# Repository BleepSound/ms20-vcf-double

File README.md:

[![CC BY-SA 4.0][cc-by-sa-shield]][cc-by-sa]

# Double MS20-VCF

Latest documentation available at https://bleepsound.github.io/modules/

This work is licensed under a
[Creative Commons Attribution-ShareAlike 4.0 International License][cc-by-sa].

[![CC BY-SA 4.0][cc-by-sa-image]][cc-by-sa]

[cc-by-sa]: http://creativecommons.org/licenses/by-sa/4.0/
[cc-by-sa-image]: https://licensebuttons.net/l/by-sa/4.0/88x31.png
[cc-by-sa-shield]: https://img.shields.io/badge/License-CC%20BY--SA%204.0-lightgrey.svg

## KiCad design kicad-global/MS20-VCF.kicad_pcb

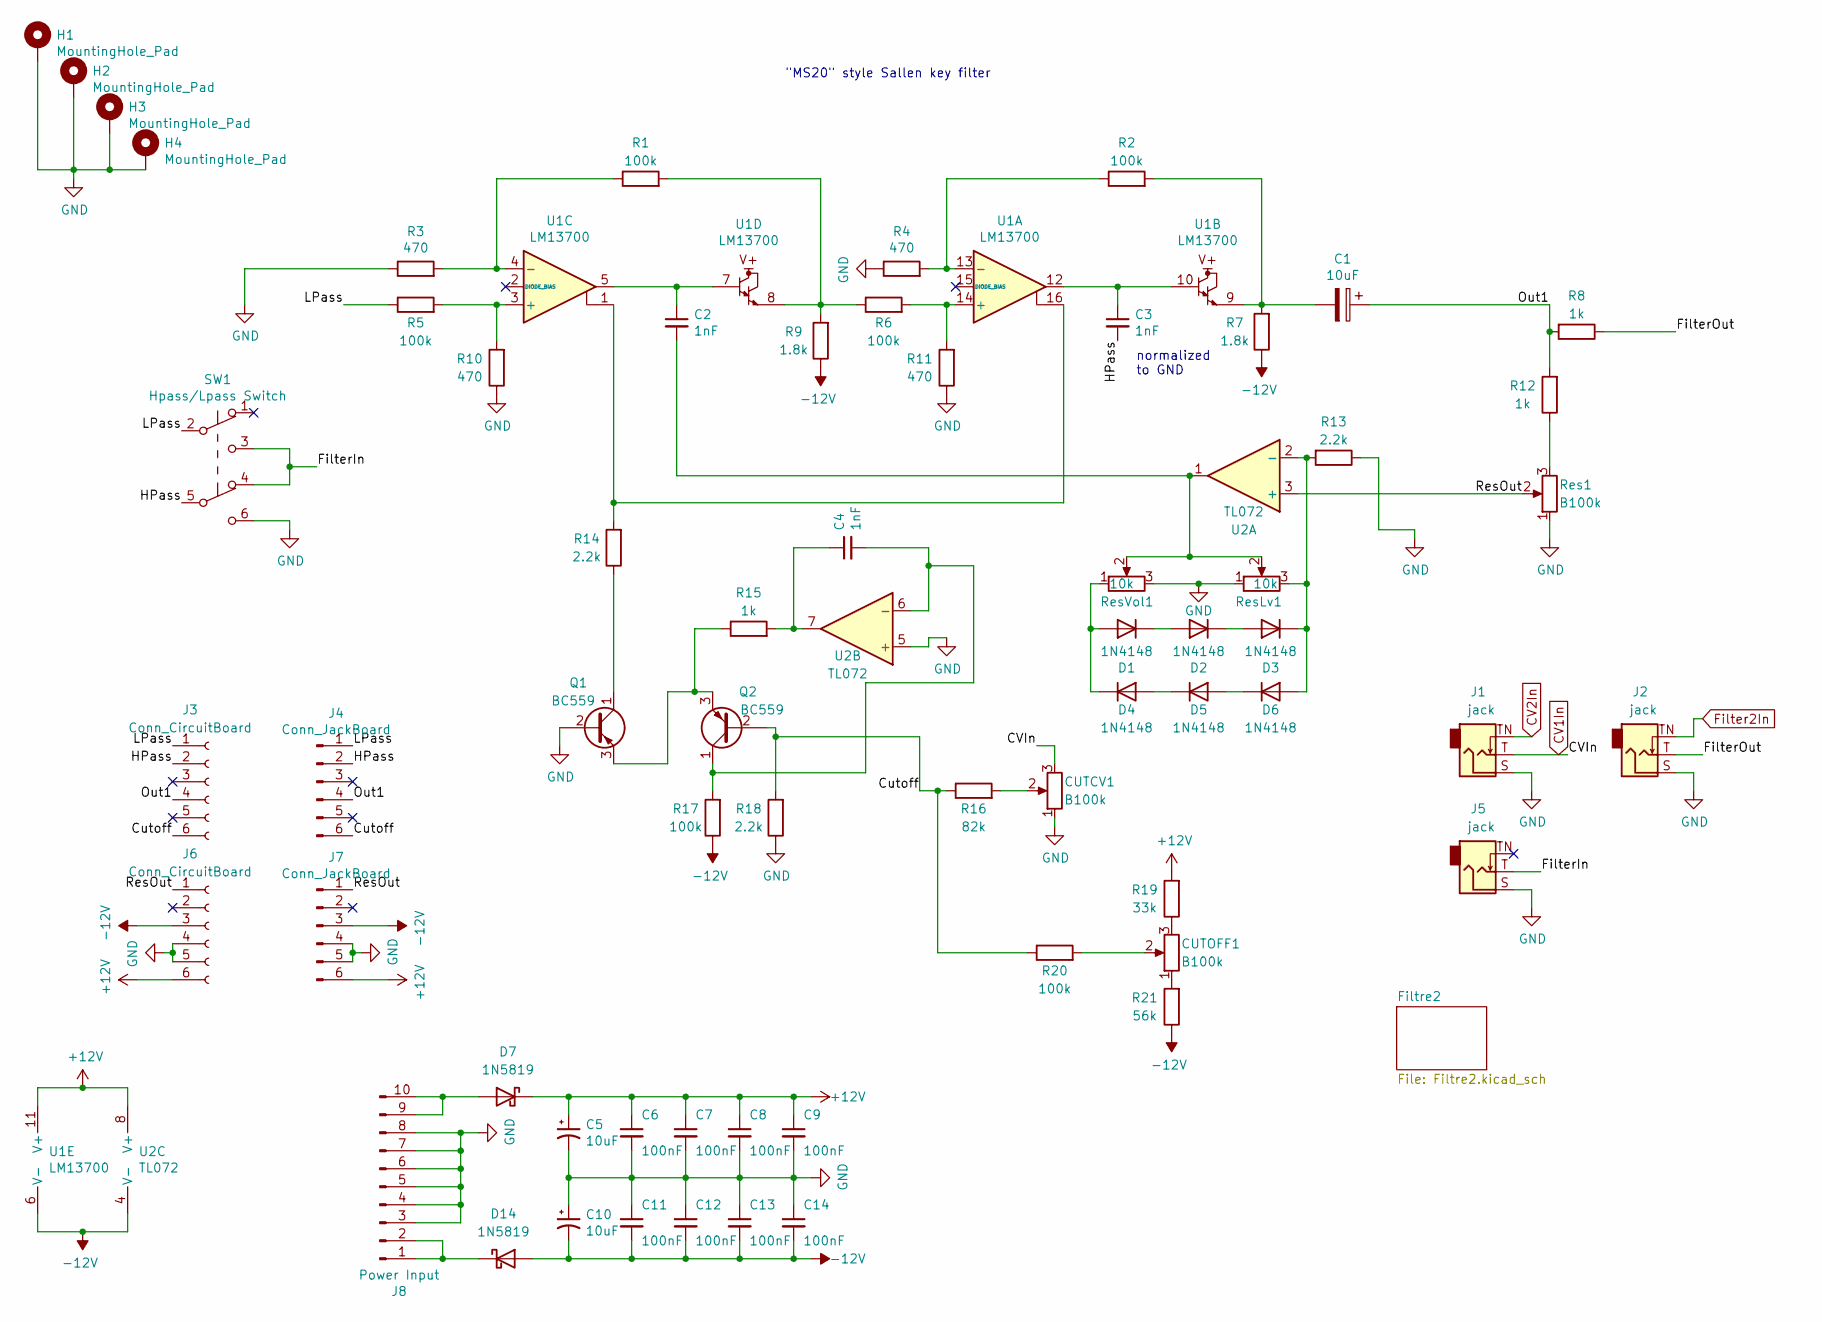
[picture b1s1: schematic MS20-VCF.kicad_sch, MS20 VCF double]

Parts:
C1, C5, C10: 10uF; CP_Radial_D5.0mm_P2.00mm
C2, C3, C4: 1nF; C_Disc_D7.0mm_W2.5mm_P5.00mm
C6, C7, C8, C9, C11, C12, C13, C14: 100nF; C_Disc_D7.0mm_W2.5mm_P5.00mm
CUTCV1: B100k; Pot-bourns-alpha
CUTOFF1: B100k; Pot-bourns-alpha
D1, D2, D3, D4, D5, D6: 1N4148; D_DO-35_SOD27_P7.62mm_Horizontal
D7, D14: 1N5819; D_DO-41_SOD81_P10.16mm_Horizontal
H1, H2, H3, H4: MountingHole_Pad; Doepfer Mounting hole
J1, J2, J5: jack; Thonkiconn
J3, J6: Conn_CircuitBoard; PinSocket_1x06_P2.54mm_Vertical
J4, J7: Conn_JackBoard; PinHeader_1x06_P2.54mm_Vertical
J8: Power Input; IDC-Header_2x05_P2.54mm_Vertical
Q1, Q2: BC559; TO-92_Inline_Wide
R1, R2, R5, R6, R17, R20: 100k; R_Axial_DIN0207_L6.3mm_D2.5mm_P10.16mm_Horizontal
R3, R4, R10, R11: 470; R_Axial_DIN0207_L6.3mm_D2.5mm_P10.16mm_Horizontal
R7, R9: 1.8k; R_Axial_DIN0207_L6.3mm_D2.5mm_P10.16mm_Horizontal
R8, R12, R15: 1k; R_Axial_DIN0207_L6.3mm_D2.5mm_P10.16mm_Horizontal
R13, R14, R18: 2.2k; R_Axial_DIN0207_L6.3mm_D2.5mm_P10.16mm_Horizontal
R16: 82k; R_Axial_DIN0207_L6.3mm_D2.5mm_P10.16mm_Horizontal
R19: 33k; R_Axial_DIN0207_L6.3mm_D2.5mm_P10.16mm_Horizontal
R21: 56k; R_Axial_DIN0207_L6.3mm_D2.5mm_P10.16mm_Horizontal
Res1: B100k; Pot-bourns-alpha
ResLv1: 10k; Potentiometer_Bourns_3296W_Vertical
ResVol1: 10k; Potentiometer_Bourns_3296W_Vertical
SW1: Hpass/Lpass Switch; SW_DPDT_Toggle
U1: LM13700; SOIC-16_3.9x9.9mm_P1.27mm
U2: TL072; DIP-8_W7.62mm_Socket

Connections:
+12V: C5.1, C6.1, C7.1, C8.1, C9.1, D7.1 (K), J6.6, J7.6, R19.2, U1.11 (V+), U2.8 (V+); also elsewhere on the board
-12V: C10.2, C11.2, C12.2, C13.2, C14.2, D14.2 (A), J6.3, J7.3, R7.1, R9.1, R17.1, R21.1, U1.6 (V-), U2.4 (V-); also elsewhere on the board
/Cutoff: J3.6, J4.6, Q2.2 (B), R16.1, R18.2, R20.1
/FilterIn: J5.T, SW1.3 (C), SW1.4 (A)
/FilterOut: J2.T, R8.1
/HPass: C3.2, J3.2, J4.2, SW1.5 (B)
/LPass: J3.1, J4.1, R5.1, SW1.2 (B)
/Out1: C1.1, J3.4, J4.4, R8.2, R12.2
/ResOut: J6.1, J7.1, Res1.2, U2.3 (+)
CV1In: CUTCV1.3, J1.T; also elsewhere on the board
CV2In: J1.TN; also elsewhere on the board
Filter2In: J2.TN; also elsewhere on the board
GND: C5.2, C6.2, C7.2, C8.2, C9.2, C10.1, C11.1, C12.1, C13.1, C14.1, CUTCV1.1, H1.1, H2.1, H3.1, H4.1, J1.S, J2.S, J5.S, J6.4, J6.5, J7.4, J7.5, J8.3, J8.4, J8.5, J8.6, J8.7, J8.8, Q1.2 (B), R3.1, R4.1, R10.1, R11.1, R13.1, R18.1, Res1.1, ResLv1.1, ResVol1.3, SW1.6 (C), U2.5 (+); also elsewhere on the board
unnamed: C1.2, R2.2, R7.2, U1.9
unnamed: C2.1, U1.5, U1.7
unnamed: C2.2, ResLv1.2, ResVol1.2, U2.1
unnamed: C3.1, U1.10, U1.12
unnamed: C4.1, R15.2, U2.7
unnamed: CUTCV1.2, R16.2
unnamed: CUTOFF1.1, R21.2
unnamed: CUTOFF1.2, R20.2
unnamed: CUTOFF1.3, R19.1
unnamed: D1.2 (A), D4.1 (K), ResVol1.1
unnamed: D1.1 (K), D2.2 (A)
unnamed: D2.1 (K), D3.2 (A)
unnamed: D3.1 (K), D6.2 (A), R13.2, ResLv1.3, U2.2 (-)
unnamed: D4.2 (A), D5.1 (K)
unnamed: D5.2 (A), D6.1 (K)
unnamed: D7.2 (A), J8.9, J8.10
unnamed: D14.1 (K), J8.1, J8.2
unnamed: Q1.1 (C), R14.1
unnamed: Q1.3 (E), Q2.3 (E), R15.1
unnamed: C4.2, Q2.1 (C), R17.2, U2.6 (-)
unnamed: R1.2, R6.1, R9.2, U1.8
unnamed: R12.1, Res1.3
unnamed: R14.2, U1.1, U1.16
unnamed: R6.2, R11.2, U1.14 (+)
unnamed: R2.1, R4.2, U1.13 (-)
unnamed: R5.2, R10.2, U1.3 (+)
unnamed: R1.1, R3.2, U1.4 (-)

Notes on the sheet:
normalized to GND
"MS20" style Sallen key filter

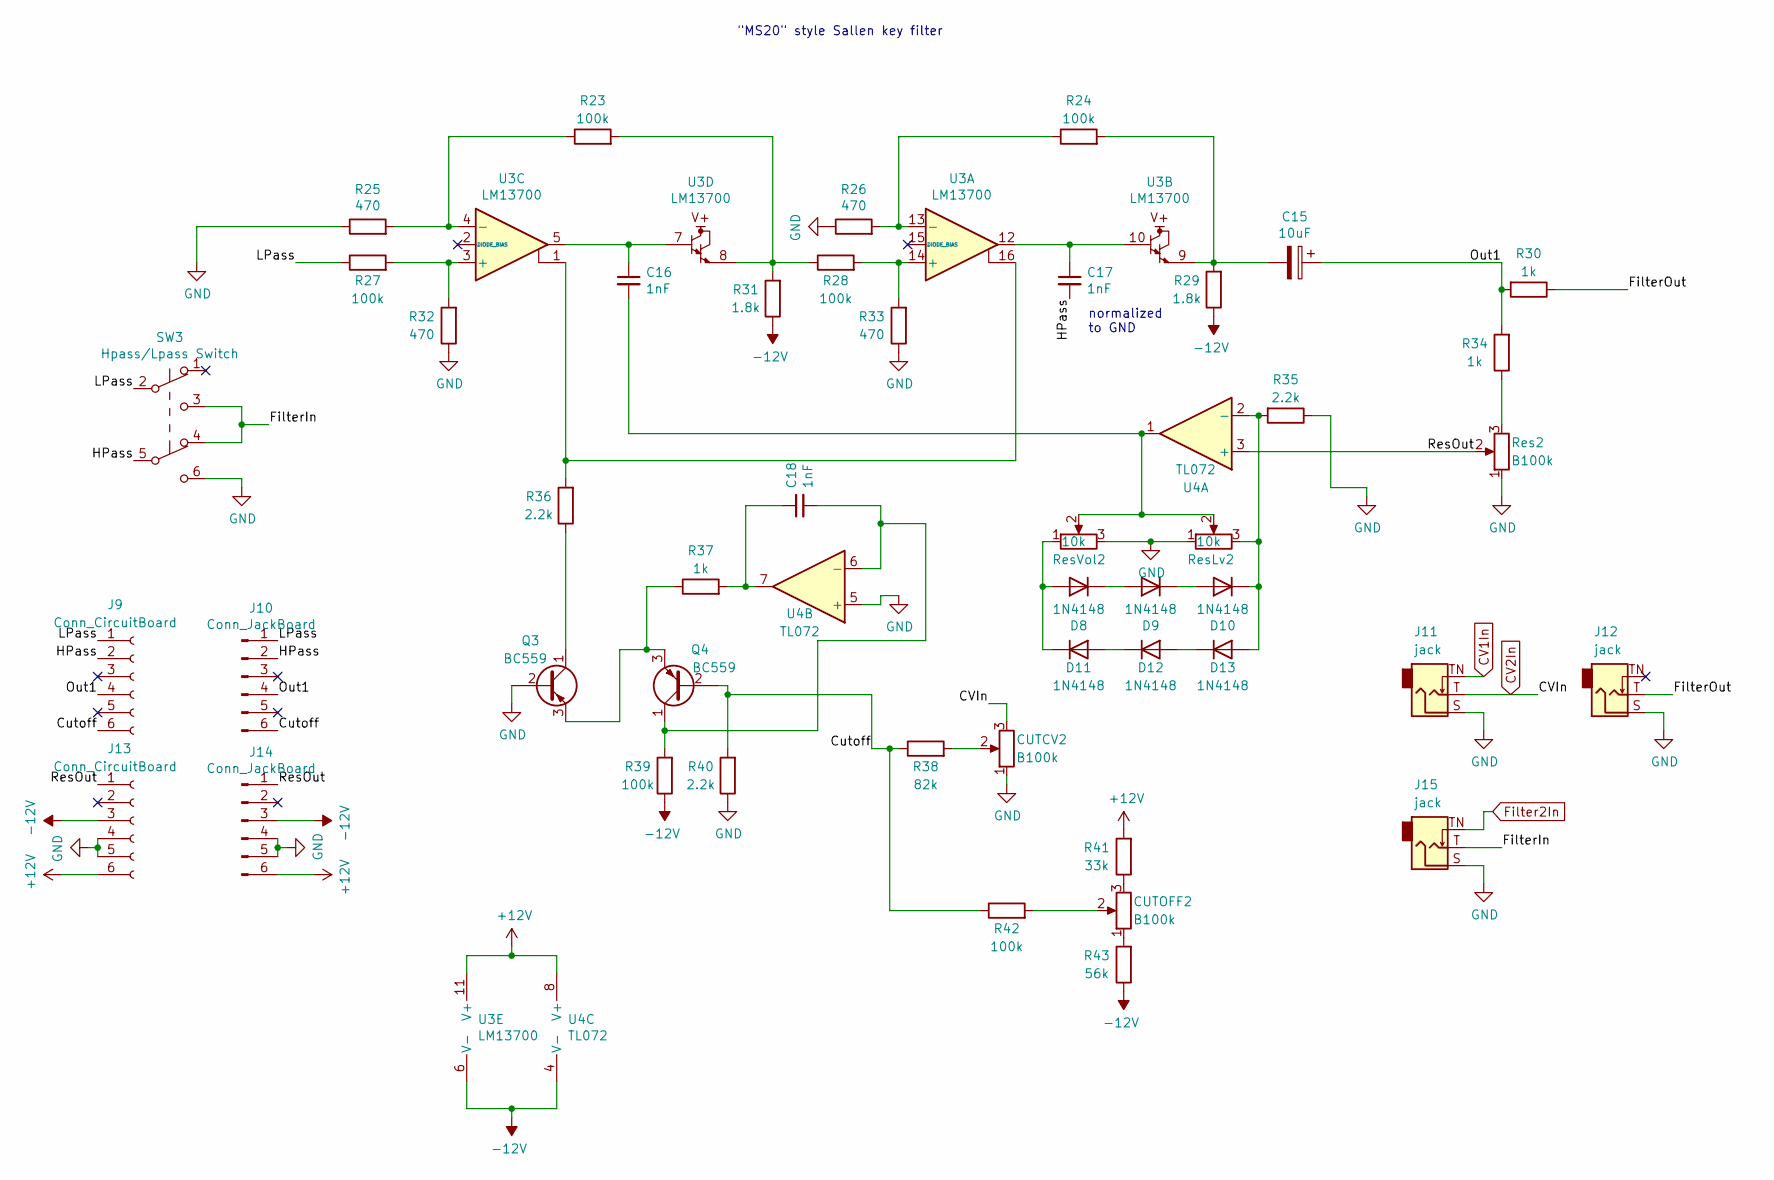
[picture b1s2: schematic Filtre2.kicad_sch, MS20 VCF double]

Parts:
C15: 10uF; CP_Radial_D5.0mm_P2.00mm
C16, C17, C18: 1nF; C_Disc_D7.0mm_W2.5mm_P5.00mm
CUTCV2: B100k; Pot-bourns-alpha
CUTOFF2: B100k; Pot-bourns-alpha
D8, D9, D10, D11, D12, D13: 1N4148; D_DO-35_SOD27_P7.62mm_Horizontal
J9, J13: Conn_CircuitBoard; PinSocket_1x06_P2.54mm_Vertical
J10, J14: Conn_JackBoard; PinHeader_1x06_P2.54mm_Vertical
J11, J12, J15: jack; Thonkiconn
Q3, Q4: BC559; TO-92_Inline_Wide
R23, R24, R27, R28, R39, R42: 100k; R_Axial_DIN0207_L6.3mm_D2.5mm_P10.16mm_Horizontal
R25, R26, R32, R33: 470; R_Axial_DIN0207_L6.3mm_D2.5mm_P10.16mm_Horizontal
R29, R31: 1.8k; R_Axial_DIN0207_L6.3mm_D2.5mm_P10.16mm_Horizontal
R30, R34, R37: 1k; R_Axial_DIN0207_L6.3mm_D2.5mm_P10.16mm_Horizontal
R35, R36, R40: 2.2k; R_Axial_DIN0207_L6.3mm_D2.5mm_P10.16mm_Horizontal
R38: 82k; R_Axial_DIN0207_L6.3mm_D2.5mm_P10.16mm_Horizontal
R41: 33k; R_Axial_DIN0207_L6.3mm_D2.5mm_P10.16mm_Horizontal
R43: 56k; R_Axial_DIN0207_L6.3mm_D2.5mm_P10.16mm_Horizontal
Res2: B100k; Pot-bourns-alpha
ResLv2: 10k; Potentiometer_Bourns_3296W_Vertical
ResVol2: 10k; Potentiometer_Bourns_3296W_Vertical
SW3: Hpass/Lpass Switch; SW_DPDT_Toggle
U3: LM13700; SOIC-16_3.9x9.9mm_P1.27mm
U4: TL072; DIP-8_W7.62mm_Socket

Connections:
+12V: J13.6, J14.6, R41.2, U3.11 (V+), U4.8 (V+); also elsewhere on the board
-12V: J13.3, J14.3, R29.1, R31.1, R39.1, R43.1, U3.6 (V-), U4.4 (V-); also elsewhere on the board
/Filtre2/Cutoff: J9.6, J10.6, Q4.2 (B), R38.1, R40.2, R42.1
/Filtre2/FilterIn: J15.T, SW3.3 (C), SW3.4 (A)
/Filtre2/FilterOut: J12.T, R30.1
/Filtre2/HPass: C17.2, J9.2, J10.2, SW3.5 (B)
/Filtre2/LPass: J9.1, J10.1, R27.1, SW3.2 (B)
/Filtre2/Out1: C15.1, J9.4, J10.4, R30.2, R34.2
/Filtre2/ResOut: J13.1, J14.1, Res2.2, U4.3 (+)
CV1In: J11.TN; also elsewhere on the board
CV2In: CUTCV2.3, J11.T; also elsewhere on the board
Filter2In: J15.TN; also elsewhere on the board
GND: CUTCV2.1, J11.S, J12.S, J13.4, J13.5, J14.4, J14.5, J15.S, Q3.2 (B), R25.1, R26.1, R32.1, R33.1, R35.1, R40.1, Res2.1, ResLv2.1, ResVol2.3, SW3.6 (C), U4.5 (+); also elsewhere on the board
unnamed: C15.2, R24.2, R29.2, U3.9
unnamed: C16.1, U3.5, U3.7
unnamed: C16.2, ResLv2.2, ResVol2.2, U4.1
unnamed: C17.1, U3.10, U3.12
unnamed: C18.1, R37.2, U4.7
unnamed: CUTCV2.2, R38.2
unnamed: CUTOFF2.1, R43.2
unnamed: CUTOFF2.2, R42.2
unnamed: CUTOFF2.3, R41.1
unnamed: D8.1 (K), D9.2 (A)
unnamed: D9.1 (K), D10.2 (A)
unnamed: D10.1 (K), D13.2 (A), R35.2, ResLv2.3, U4.2 (-)
unnamed: D11.2 (A), D12.1 (K)
unnamed: D8.2 (A), D11.1 (K), ResVol2.1
unnamed: D12.2 (A), D13.1 (K)
unnamed: Q3.1 (C), R36.1
unnamed: Q3.3 (E), Q4.3 (E), R37.1
unnamed: C18.2, Q4.1 (C), R39.2, U4.6 (-)
unnamed: R23.2, R28.1, R31.2, U3.8
unnamed: R34.1, Res2.3
unnamed: R36.2, U3.1, U3.16
unnamed: R28.2, R33.2, U3.14 (+)
unnamed: R24.1, R26.2, U3.13 (-)
unnamed: R27.2, R32.2, U3.3 (+)
unnamed: R23.1, R25.2, U3.4 (-)

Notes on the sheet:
normalized to GND
"MS20" style Sallen key filter

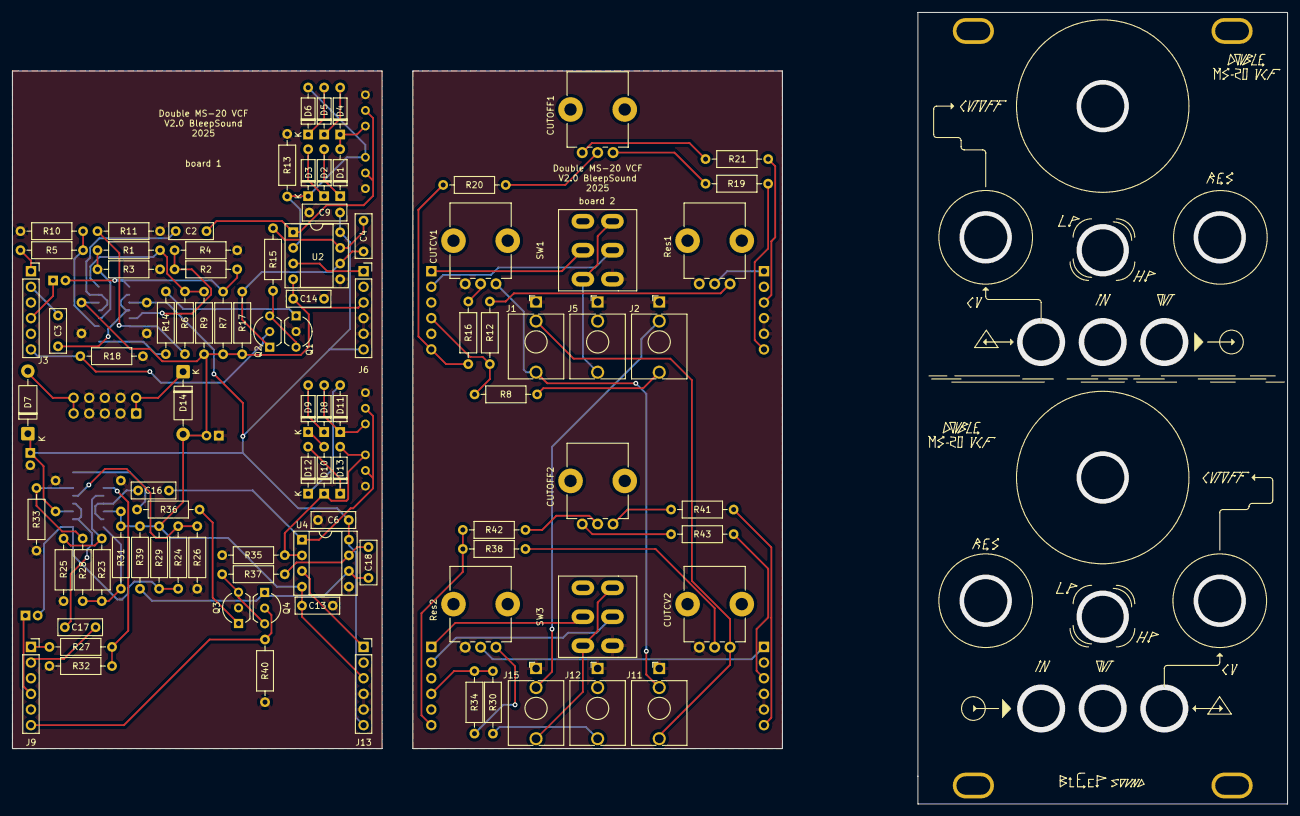
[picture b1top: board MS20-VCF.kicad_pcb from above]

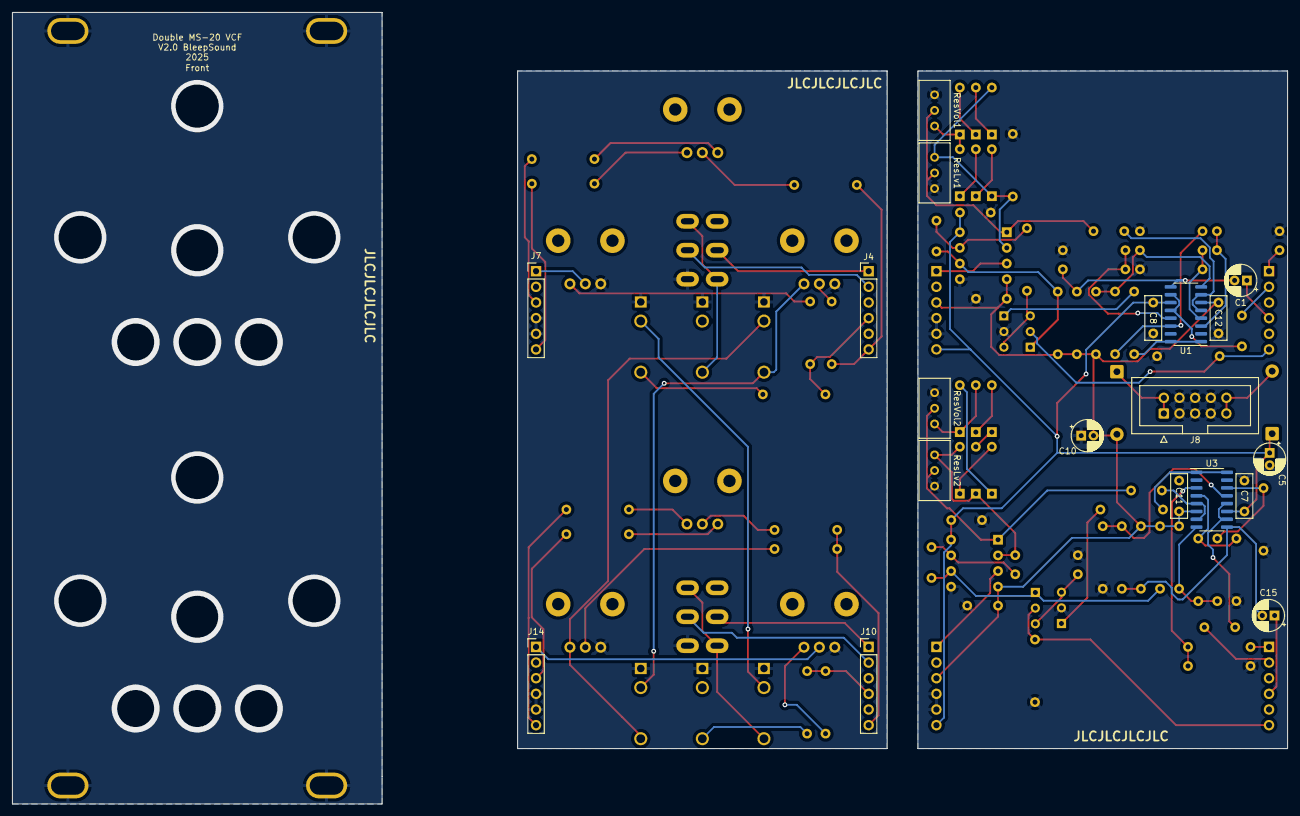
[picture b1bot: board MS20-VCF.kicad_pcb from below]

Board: 2 copper layers, 207.0 x 128.5 mm, 113 parts (19 on the bottom side), 72 nets.

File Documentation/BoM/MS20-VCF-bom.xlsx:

|  | KiBot Bill of Materials
 |  | Schematic: | MS20-VCF | Component Groups: | 28
 |  | Variant: | default | Component Count: | 112 (2 SMD/ 110 THT)
 |  | Revision: |  | Fitted Components: | 112 (2 SMD/ 110 THT)
 |  | Date: | 2023-01-12_18-11-16 | Number of PCBs: | 1
 |  | KiCad Version: | 6.0.10+dfsg-1~bpo11+1 | Total Components: | 112
Row | Description | References | Value | Quantity Per PCB | Comment
1 | Unpolarized capacitor, small symbol | C2 C3 C4 C16 C17 C18 | 1nF | 6
2 | Unpolarized capacitor, small symbol | C6 C7 C8 C9 C11 C12 C13 C14 | 100nF | 8
3 |  | C1 C15 | 10µF | 2
4 |  | C5 C10 | 10µ | 2
5 |  | CUTCV1 CUTCV2 CUTOFF1 CUTOFF2 Res1 Res2 | 100k | 6
6 | Diode | D1 D2 D3 D4 D5 D6 D8 D9 D10 D11 D12 D13 | 1N4148 | 12
7 | Light emitting diode | D7 | LED-12V | 1
8 |  | FB1 FB2 | 10R | 2
9 | Generic connector, single row, 01x06, script generated (kicad-library-utils/sch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 | J3 J6 J9 J13 | Conn_CircuitBoard | 4
10 | Generic connector, single row, 01x06, script generated (kicad-library-utils/sch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 | J4 J7 J10 J14 | Conn_JackBoard | 4
11 | Audio Jack, 2 Poles (Mono / TS), Switched Pole (Normalling) | J1 J2 J5 J11 J12 J15 | FilterCV1 | 6
12 | Generic connector, single row, 01x10, script generated (kicad-library-utils/sch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 | J8 | Power Input | 1
13 | 0.1A Ic, 30V Vce, PNP Small Signal Transistor, TO-92 | Q1 Q2 Q3 Q4 | BC559 | 4
14 | Resistor | R3 R4 R10 R11 R25 R26 R32 R33 | 470 | 8
15 | Resistor | R8 R12 R15 R30 R34 R37 | 1k | 6
16 | Resistor | R7 R9 R29 R31 | 1.8k | 4
17 | Resistor | R13 R14 R18 R22 R35 R36 R40 | 2.2k | 7
18 | Resistor | R19 R41 | 33k | 2
19 | Resistor | R21 R43 | 56k | 2
20 | Resistor | R16 R38 | 82k | 2
21 | Resistor | R1 R2 R5 R6 R17 R20 R23 R24 R27 R28 R39 R42 | 100k | 12
22 |  | ResLv2 | 3.3k | 1
23 |  | ResLv1 | 5k | 1
24 |  | ResVol1 ResVol2 | 10k | 2
25 | Switch, single pole double throw | SW2 | Bandpass | 1
26 | Momentary Switch, dual pole double throw | SW1 SW3 | Hpass/Lpass Switch | 2
27 | Dual Operational Transconductance Amplifiers with Linearizing Diodes and Buffer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 | U1 U3 | LM13700 | 2
28 | Dual Low-Noise JFET-Input Operational Amplifiers, DIP-8/SOIC-8 | U2 U4 | TL072 | 2

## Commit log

2023-01-12 initial commit with all files and workflows updated
2023-01-12 add circuit BoM
2023-01-12 add front gerber
2023-01-12 add main BoM and images
2023-01-12 add jack BoM
2023-01-12 add jack gerber
2023-01-12 fix issues and add guide
2023-01-12 add circuit gerber
2023-01-12 update image link
2023-01-13 Remove jekyll workflow
2023-01-20 update bom file
2023-01-31 update gitignore
2023-02-18 update worflow run condition + trimmer footprint update
2023-02-18 Add minimal-mistakes-jekyll theme
2023-02-18 Add setup-ruby action to jekyll-gh-pages.yml
2023-02-19 Trigger on pull request
2023-02-19 fixup! Trigger on pull request
2023-02-19 Add ruby version file
2023-03-16 update value for trimmer
2023-06-10 update front panel and infos on components
2023-06-10 update kibot script to work on latest version
2023-06-10 fix issue with kibot to use kicad 7
2023-06-10 comment fab guide because of dependency problem fro gitactions
2023-09-23 update documentation + update repo layout
2023-10-15 update version number + hole size on front panel
2023-11-05 fix issue with links on readme
2023-12-10 add extra info for bom
2024-10-19 update theme to remote
2024-10-19 update workflow action versions
2024-10-19 add cmd for deploy on push
2024-10-19 add link to download BOM in Excel
2024-10-26 stop github pages hosting
2025-10-28 V2.0
    new front panel layout
    new normalisation for CV and in/out for bandpass filter
2025-10-28 update readme
    add link to latest doc on website
2025-11-27 add licence
